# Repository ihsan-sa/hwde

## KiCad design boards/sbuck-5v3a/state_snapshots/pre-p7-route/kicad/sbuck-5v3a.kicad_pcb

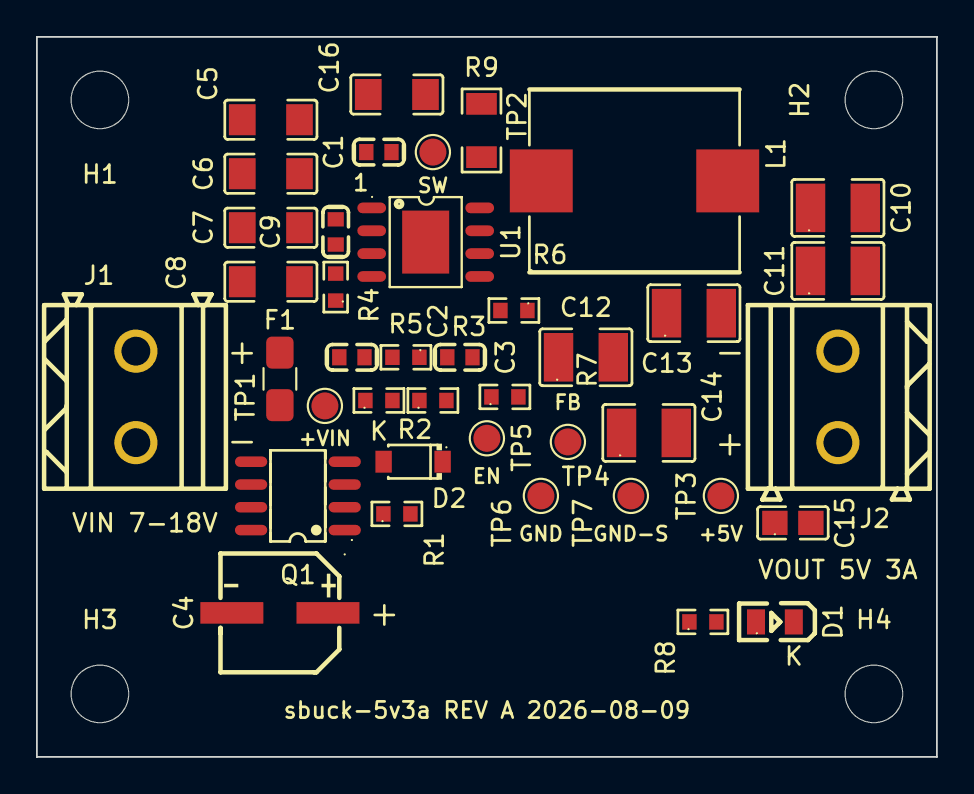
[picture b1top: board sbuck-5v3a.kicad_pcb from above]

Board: 4 copper layers, 50.0 x 40.0 mm, 44 parts (0 on the bottom side), 15 nets, no tracks yet.

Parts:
C1, C9: 100nF 50V X7R; C0603
C2: 3.3nF 50V X7R; C0603
C3: 10pF 50V C0G; C0603
C4: 100uF 35V 80mOhm; CAP-SMD_BD6.3-L6.5-W6.5-LS7.2-FD
C5, C6, C7, C8: 4.7uF 50V X7R; C1206
C10, C11, C12, C13, C14: 22uF 25V X7R; C1210
C15: 4.7uF 16V X7R; C0805
C16: 470pF 1kV C0G; C1206
D1: GREEN; LED0805-R-RD
D2: BZT52C15 15V; SOD-123_L2.7-W1.6-LS3.7-RD
F1: 5A slow-blow; Fuse_1206_C1T_BelVendorLand
H1, H2, H3, H4: M3_3.2mm; MountingHole_3.2mm_M3
J1, J2: SCREW_5.08_2P; CONN-TH_2P-P5.08_DB128L-5.08-2P
L1: 6.8uH; IND-SMD_L11.5-W10.0
Q1: AO4407A; SOIC-8_L4.9-W3.9-P1.27-LS6.0-BL
R1: 100k 1%; R0603
R2: 105k 1%; R0603
R3: 24.0k 1%; R0603
R4: 200k 1%; R0603
R5: 75k 1%; R0603
R6: 105k 0.1%; R0603
R7: 20.0k 0.1%; R0603
R8: 2.2k 1%; R0603
R9: 22R 1% 0.25W; R1206
TP1: +VIN; TestPoint_Pad_D1.5mm
TP2: SW; TestPoint_Pad_D1.5mm
TP3: +5V; TestPoint_Pad_D1.5mm
TP4: FB; TestPoint_Pad_D1.5mm
TP5: EN; TestPoint_Pad_D1.5mm
TP6, TP7: GND; TestPoint_Pad_D1.5mm
U1: AP64350SP-13; SO-8_L4.9-W3.9-P1.27-LS6.0-BL-EP

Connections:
+5V: C10.1, C11.1, C12.1, C13.1, C14.1, C15.1, J2.1, L1.2, R6.1, R8.1, TP3.1
+VIN: C4.1, C5.1, C6.1, C7.1, C8.1, C9.1, D2.1, Q1.1, Q1.2, Q1.3, R2.1, TP1.1, U1.2
/BST: C1.1, U1.1
/COMP: C3.1, R5.1, U1.6
/COMPZ: C2.1, R5.2
/EN: R2.2, R3.1, TP5.1, U1.3
/FB: R6.2, R7.1, TP4.1, U1.5
/LEDA: D1.1, R8.2
/QGATE: D2.2, Q1.4, R1.1
/RT: R4.1, U1.4
/SNUBZ: C16.1, R9.2
/SW: C1.2, L1.1, R9.1, TP2.1, U1.8
/VIN: F1.2, Q1.5, Q1.6, Q1.7, Q1.8
/VIN_RAW: F1.1, J1.1
GND: C2.2, C3.2, C4.2, C5.2, C6.2, C7.2, C8.2, C9.2, C10.2, C11.2, C12.2, C13.2, C14.2, C15.2, C16.2, D1.2, J1.2, J2.2, R1.2, R3.2, R4.2, R7.2, TP6.1, TP7.1, U1.7, U1.9

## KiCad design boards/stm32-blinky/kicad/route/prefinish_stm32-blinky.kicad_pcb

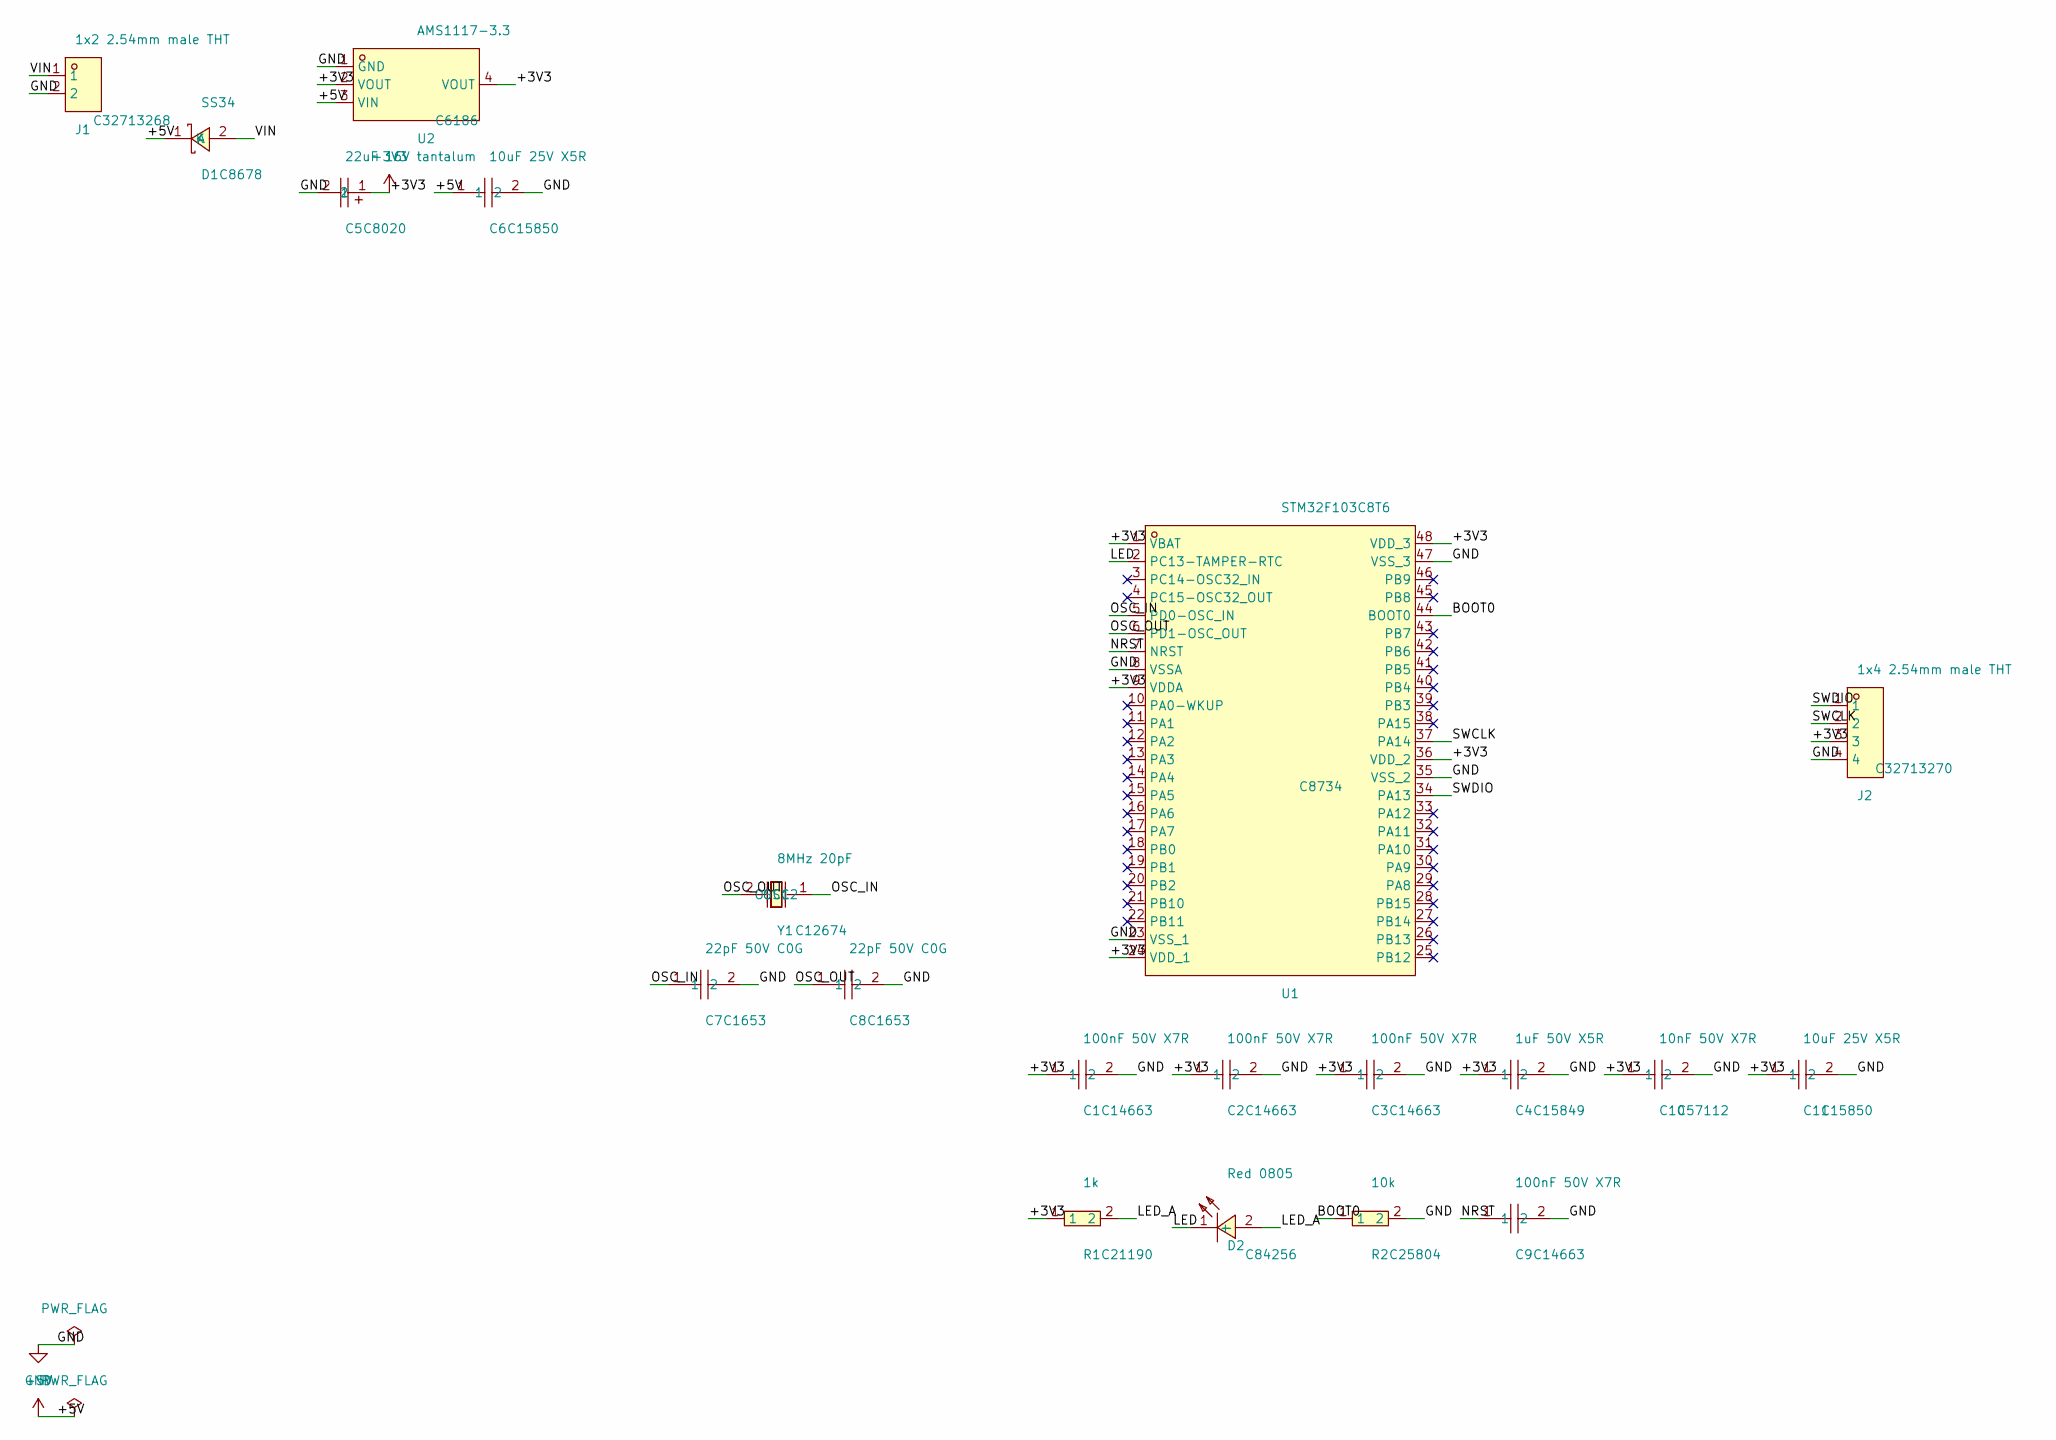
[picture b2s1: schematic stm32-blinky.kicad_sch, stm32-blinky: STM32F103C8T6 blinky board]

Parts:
C1, C2, C3, C9: 100nF 50V X7R; C0603; LCSC C14663
C4: 1uF 50V X5R; C0603; LCSC C15849
C5: 22uF 16V tantalum; CASE-B_3528; LCSC C8020
C6, C11: 10uF 25V X5R; C0805; LCSC C15850
C7, C8: 22pF 50V C0G; C0603; LCSC C1653
C10: 10nF 50V X7R; C0603; LCSC C57112
D1: SS34; SMA_L4.3-W2.6-LS5.2-RD; LCSC C8678
D2: Red 0805; LED0805-RD; LCSC C84256
J1: 1x2 2.54mm male THT; HDR-TH_2P-P2.54-V-M-3; LCSC C32713268
J2: 1x4 2.54mm male THT; HDR-TH_4P-P2.54-V-M; LCSC C32713270
R1: 1k; R0603; LCSC C21190
R2: 10k; R0603; LCSC C25804
U1: STM32F103C8T6; LQFP-48_L7.0-W7.0-P0.50-LS9.0-BL; LCSC C8734
U2: AMS1117-3.3; SOT-223-3_L6.5-W3.4-P2.30-LS7.0-BR; LCSC C6186
Y1: 8MHz 20pF; CRYSTAL-SMD_L11.5-W4.8-LS12.7; LCSC C12674

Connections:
+3V3: C1.1, C2.1, C3.1, C4.1, C5.1, C10.1, C11.1, J2.3, R1.1, U1.1 (VBAT), U1.9 (VDDA), U1.24 (VDD_1), U1.36 (VDD_2), U1.48 (VDD_3), U2.2 (VOUT), U2.4 (VOUT)
+5V: C6.1, D1.1 (K), U2.3 (VIN)
/BOOT0: R2.1, U1.44 (BOOT0)
/LED: D2.1 (-), U1.2 (PC13-TAMPER-RTC)
/LED_A: D2.2 (+), R1.2
/NRST: C9.1, U1.7 (NRST)
/OSC_IN: C7.1, U1.5 (PD0-OSC_IN), Y1.1 (OSC1)
/OSC_OUT: C8.1, U1.6 (PD1-OSC_OUT), Y1.2 (OSC2)
/SWCLK: J2.2, U1.37 (PA14)
/SWDIO: J2.1, U1.34 (PA13)
/VIN: D1.2 (A), J1.1
GND: C1.2, C2.2, C3.2, C4.2, C5.2, C6.2, C7.2, C8.2, C9.2, C10.2, C11.2, J1.2, J2.4, R2.2, U1.8 (VSSA), U1.23 (VSS_1), U1.35 (VSS_2), U1.47 (VSS_3), U2.1 (GND)

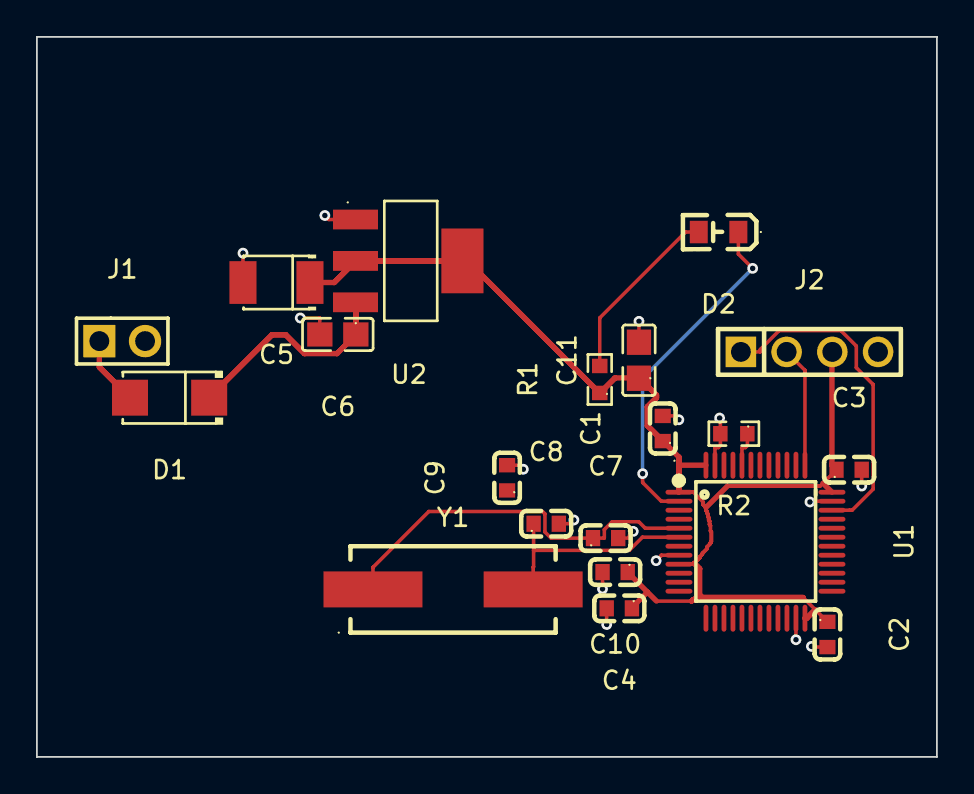
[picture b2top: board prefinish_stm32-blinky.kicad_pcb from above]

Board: 2 copper layers, 50.0 x 40.0 mm, 20 parts (0 on the bottom side), 12 nets.
